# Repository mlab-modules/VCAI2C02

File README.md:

# VCAI2C02A

## Overview

The VCAI2C02A is an I2C module designed for measuring current (0-50A) and voltage (0-50V) using a measuring transformer. It integrates multiple components to provide accurate and reliable measurements for various applications.

## Features

- **Current Measurement:** 0 to 50A
- **Voltage Measurement:** 0 to 50V
- **Interface:** I2C
- **Measurement Transformer:** Included
- **Connectors:** XT30PW-M and XT30PW-F
- **High Stability Isolated Error Amplifier:** ADuM3190
- **High-Resolution ADC:** MCP3423

## Components

### XT30PW Connectors

- **Item No:** XT30PW-M and XT30PW-F
- **Contact Resistance:** 0.80mΩ
- **Rated Voltage:** DC 500V
- **Rated Current:** 15A
- **Instantaneous Current:** 30A
- **Material:** Brass Gold Plated
- **Insulation Material:** PA, UL94 V0
- **Operating Temperature:** -20℃ to 120℃

### ADuM3190 Isolated Error Amplifier

- **Stability in isolated feedback applications**
- **Initial Accuracy:** 0.5%
- **Accuracy over Temperature Range:** 1%
- **Reference Voltage:** 1.225V
- **Bandwidth:** 400 kHz
- **Isolation Voltage:** 2.5 kV rms
- **Temperature Range:** -40°C to +125°C

### MCP3423 ADC

- **Resolution:** 18-bit
- **Interface:** I2C
- **Programmable Data Rate**
- **Internal Voltage Reference:** 2.048V

### Hall Effect Current Sensor (Tamura L01ZXXXS05 Series)

- **Type:** Open Loop
- **Mounting:** PCB
- **Nominal Current:** Up to 600A
- **Accuracy:** Excellent accuracy and linearity
- **Temperature Drift:** Low
- **Frequency Bandwidth:** Wide
- **No Insertion Loss**

## Applications

- **Linear Power Supplies**
- **Inverters**
- **Uninterruptible Power Supply (UPS)**
- **DOSA-compatible Modules**
- **Voltage Monitors**
- **Automotive and drone Systems**

## Additional Resources

For more detailed information, please refer to the datasheets of the components used in the VCAI2C02A module:

- [ADuM3190 Datasheet](https://www.analog.com/media/en/technical-documentation/data-sheets/ADuM3190.pdf)
- [MCP3423 Datasheet](https://www.microchip.com/wwwproducts/en/MCP3423)
- [XT30PW Connectors Specification](http://www.china-amass.com/)

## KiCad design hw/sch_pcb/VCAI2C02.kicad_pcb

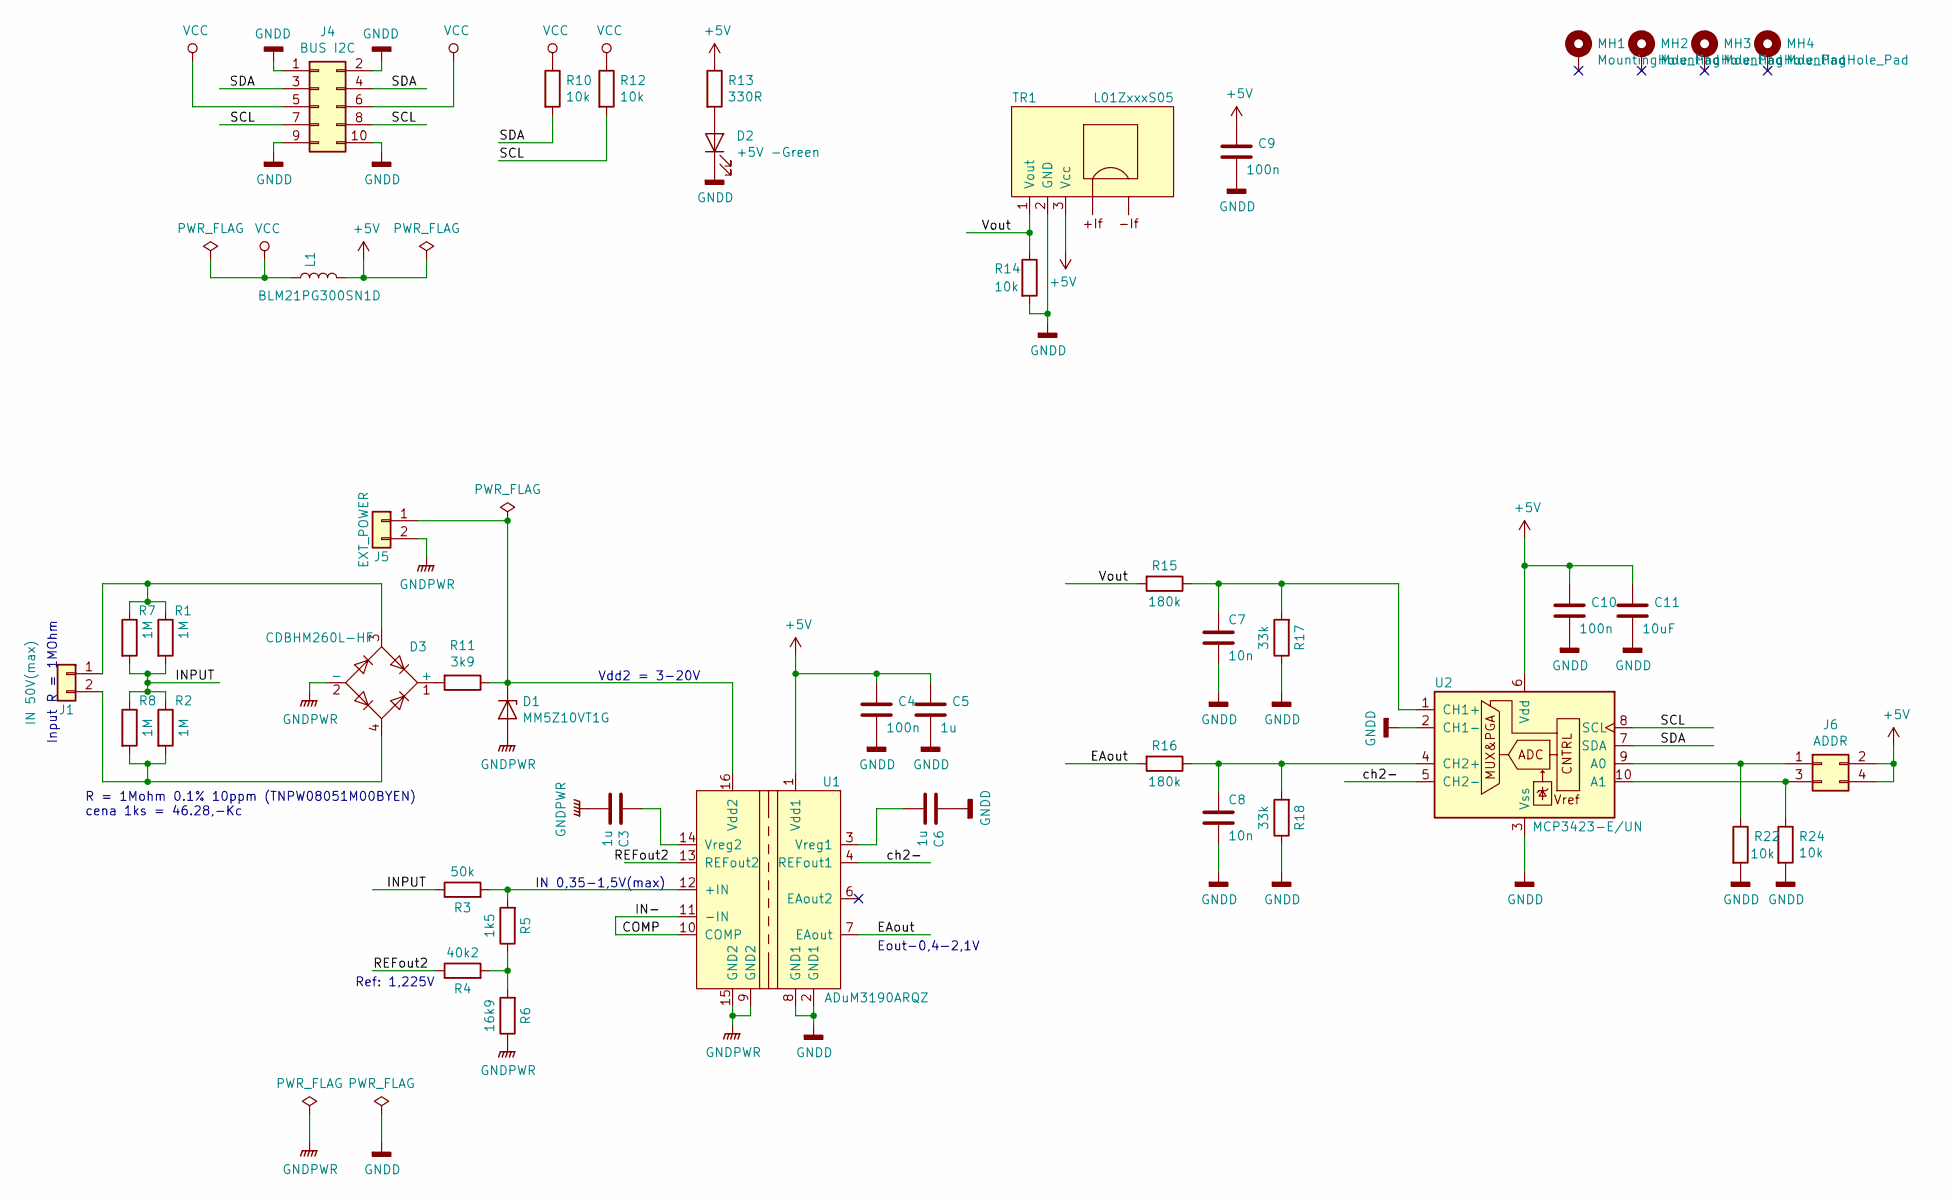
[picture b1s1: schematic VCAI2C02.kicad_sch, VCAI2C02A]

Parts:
C3, C5, C6: 1u; C_0805_2012Metric
C4, C9, C10: 100n; C_0805_2012Metric
C7, C8: 10n; C_0805_2012Metric
C11: 10uF; CP_EIA-3528-21_Kemet-B
D1: MM5Z10VT1G; D_SOD-523
D2: +5V -Green; LED_1206
D3: CDBHM260L-HF; MSB-2
J1: IN 50V(max); XT30PW-M
J4: BUS I2C; Straight_2x05
J5: EXT_POWER; Straight_2x01
J6: ADDR; Straight_2x02
L1: BLM21PG300SN1D; BLM21PG_3Amp
MH1, MH2, MH3, MH4: MountingHole_Pad; MountingHole_3mm
R1, R2, R7, R8: 1M; R_0805_2012Metric
R3: 50k; R_0805_2012Metric
R4: 40k2; R_0805_2012Metric
R5: 1k5; R_0805_2012Metric
R6: 16k9; R_0805_2012Metric
R10, R12, R14, R22, R24: 10k; R_0805_2012Metric
R11: 3k9; R_0805_2012Metric
R13: 330R; R_0805_2012Metric
R15, R16: 180k; R_0805_2012Metric
R17, R18: 33k; R_0805_2012Metric
TR1: L01ZxxxS05
U1: ADuM3190ARQZ; QSOP-16_3.9x4.9mm_P0.635mm
U2: MCP3423-E/UN; MSOP-10_3x3mm_P0.5mm

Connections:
+5V: C4.1, C5.1, C9.1, C10.1, C11.1, J6.2, J6.4, L1.2, R13.1, TR1.3 (Vcc), U1.1 (Vdd1), U2.6 (Vdd)
/COMP: U1.10 (COMP), U1.11 (-IN)
/EAout: R16.2, U1.7 (EAout)
/INPUT: R1.2, R2.1, R3.1, R7.2, R8.1
/REFout2: R4.1, U1.13 (REFout2)
/SCL: J4.7, J4.8, R12.2, U2.8 (SCL)
/SDA: J4.3, J4.4, R10.2, U2.7 (SDA)
/Vout: R14.1, R15.2, TR1.1 (Vout)
/ch2-: U1.4 (REFout1), U2.5 (CH2-)
GNDD: C4.2, C5.2, C6.1, C7.2, C8.2, C9.2, C10.2, C11.2, D2.1 (K), J4.1, J4.2, J4.9, J4.10, R14.2, R17.1, R18.1, R22.2, R24.2, TR1.2 (GND), U1.2 (GND1), U1.8 (GND1), U2.2 (CH1-), U2.3 (Vss)
GNDPWR: C3.2, D1.2 (A), D3.2 (-), J5.2, R6.1, U1.9 (GND2), U1.15 (GND2)
unnamed: C3.1, U1.14 (Vreg2)
unnamed: C6.2, U1.3 (Vreg1)
unnamed: C7.1, R15.1, R17.2, U2.1 (CH1+)
unnamed: C8.1, R16.1, R18.2, U2.4 (CH2+)
unnamed: D1.1 (K), J5.1, R11.1, U1.16 (Vdd2)
unnamed: D2.2 (A), R13.2
unnamed: D3.1 (+), R11.2
unnamed: D3.3, J1.1, R1.1, R7.1
unnamed: D3.4, J1.2, R2.2, R8.2
unnamed: J6.1, R22.1, U2.9 (A0)
unnamed: J6.3, R24.1, U2.10 (A1)
unnamed: R3.2, R5.2, U1.12 (+IN)
unnamed: R4.2, R5.1, R6.2
VCC: J4.5, J4.6, L1.1, R10.1, R12.1

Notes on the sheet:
Vdd2 = 3-20V
IN 0,35-1,5V(max)
Input R = 1MOhm
R = 1Mohm 0.1% 10ppm (TNPW08051M00BYEN) cena 1ks = 46.28,-Kc
Eout-0,4-2,1V
Ref: 1,225V

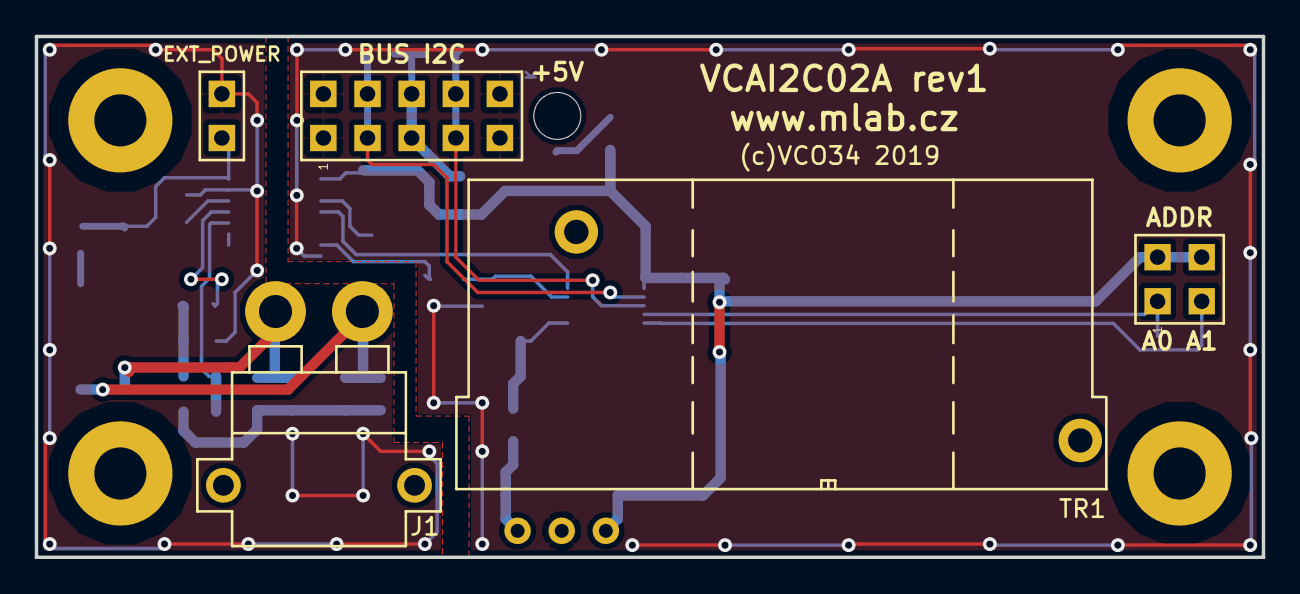
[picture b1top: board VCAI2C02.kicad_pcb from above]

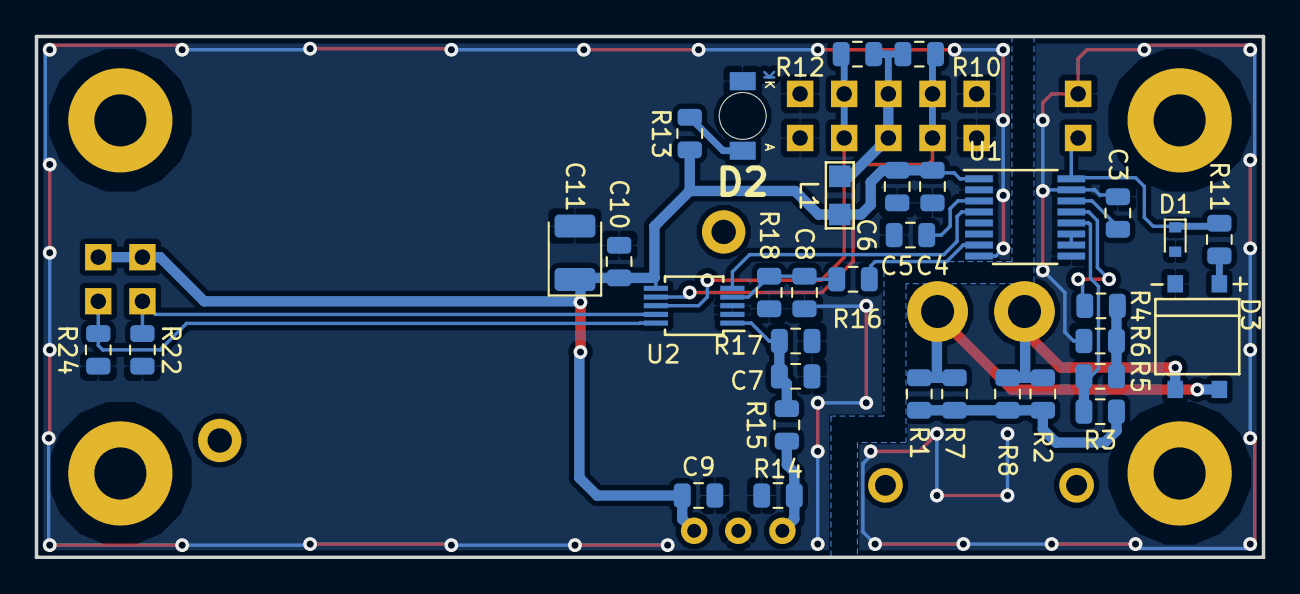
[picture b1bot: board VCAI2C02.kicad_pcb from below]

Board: 2 copper layers, 70.6 x 30.0 mm, 43 parts (34 on the bottom side), 25 nets.

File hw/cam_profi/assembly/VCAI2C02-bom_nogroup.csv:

Component,Description,Part,References,Value,Footprint,Quantity Per PCB,Datasheet,ust_id,mfpn
1,,C-Device,C7C8,10n,C_0805_2012Metric,2,,5c70984712875079b91f8b49,
2,,C-Device,C4C9C10,100n,C_0805_2012Metric,3,,5c70984712875079b91f8b4c,
3,,C-Device,C3C5C6,1u,C_0805_2012Metric,3,,5c70984812875079b91f8bc2,
4,,C-Device,C11,10uF,CP_EIA-3528-21_Kemet-B,1,,5c70984412875079b91f8865,
5,,LED-Device,D2,+5V -Green,LED_1206,1,,5c70984412875079b91f8895,
6,,D_Bridge_+-AA-Device,D3,CDBHM260L-HF,MSB-2,1,,5cb5829a1287500e61c99661,
7,,D_Zener-Device,D1,MM5Z10VT1G,D_SOD-523,1,,5cb5832e1287500e61c99679,
8,,Conn_02x02_Odd_Even-Connector_Generic,J6,ADDR,Straight_2x02,1,,,
9,,Conn_02x05_Odd_Even-Connector_Generic,J4,BUS I2C,Straight_2x05,1,,,
10,,Conn_01x02-Connector_Generic,J5,EXT_POWER,Straight_2x01,1,,,
11,,Conn_01x02-Connector_Generic,J1,IN 50V(max),XT30PW-M,1,,5c70984812875079b91f8ba8,
12,,L-Device,L1,BLM21PG300SN1D,BLM21PG_3Amp,1,,5c70984412875079b91f87fd,
13,,R-Device,R13,330R,R_0805_2012Metric,1,,5c70984512875079b91f8984,
14,,R-Device,R5,1k5,R_0805_2012Metric,1,,5c70984512875079b91f898e,
15,,R-Device,R11,3k9,R_0805_2012Metric,1,,5c70984612875079b91f8994,
16,,R-Device,R10R12R14R22R24,10k,R_0805_2012Metric,5,,5c70984612875079b91f899f,
17,,R-Device,R6,16k9,R_0805_2012Metric,1,,5cb83a291287500e61c99759,
18,,R-Device,R17R18,33k,R_0805_2012Metric,2,,5c70984712875079b91f8a8a,
19,,R-Device,R4,40k2,R_0805_2012Metric,1,,5cb839571287500e61c9974a,
20,,R-Device,R3,50k,R_0805_2012Metric,1,,5cb585391287500e61c9968c,
21,,R-Device,R15R16,180k,R_0805_2012Metric,2,,5c70984712875079b91f8a9c,
22,,R-Device,R1R2R7R8,1M,R_0805_2012Metric,4,,5c70984712875079b91f8aaa,
23,,L01ZxxxS05,TR1,L01ZxxxS05,L01ZxxxS05,1,,5cb581511287500e61c99631,L01Z100S05
24,,ADuM3190,U1,ADuM3190ARQZ,QSOP-16_3.9x4.9mm_P0.635mm,1,,5cb589091287500e61c996a0,ADuM3190ARQZ
25,,MCP3423-Analog_ADC,U2,MCP3423-E/UN,MSOP-10_3x3mm_P0.5mm,1,http://ww1.microchip.com/downloads/en/DeviceDoc/22088c.pdf,5cb589b51287500e61c996bf,MCP3423-E/UN

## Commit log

2019-03-14 [MLABweb] Documentaion edits; VCAI2C02A
2019-03-15 update schematic by comment kaklik issue #5
2019-03-15 oprava chyb, přidání compenzation network
2019-03-20 add simulation data http://www.falstad.com/circuit/circuitjs.html
2019-03-20 edit schematic by simulation
2019-03-28 DPS rev 1
2019-03-29 - doplněné přesné názvy součástek MCP a ADU integrovaného obvodu - doplněno MFPN pro měřící transformátor (100A verze) - změněny pouzdra R a C na 0805
2019-03-29 - add datasheet
2019-04-02 Generování bom.
2019-04-08 Nový modul
2019-04-08 Generování výrobních dat
2019-04-08 uprava nazvu souboru pro datasheet transformatoru
2019-04-16 Doplneno UST_ID do schema
2019-04-18 correct resistor value R4 to 40.2k, R6 to 16.9k
2019-05-24 Edit power module
2022-08-16 Update to kicad 6.0 Update titleblocks Add actions scripts.
2022-08-16 Update actions products
2023-05-25 automated commit; add github actions
2023-05-25 Update metadata files
2023-05-28 Update workflow files
2023-07-05 automated commit; rename source files to new naming convence
2023-07-05 update kicad
2023-09-16 Update image to image_title
2023-09-16 Update status
2024-07-06 Update documentation.

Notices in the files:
hw/sch_pcb/VCAI2C02.kicad_sch:
GPL 3.0
